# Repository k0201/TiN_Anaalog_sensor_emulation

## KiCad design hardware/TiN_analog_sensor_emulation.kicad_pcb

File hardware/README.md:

# TiN_Anaalog_sensor_emulation
Project for TiN at AGH 2019

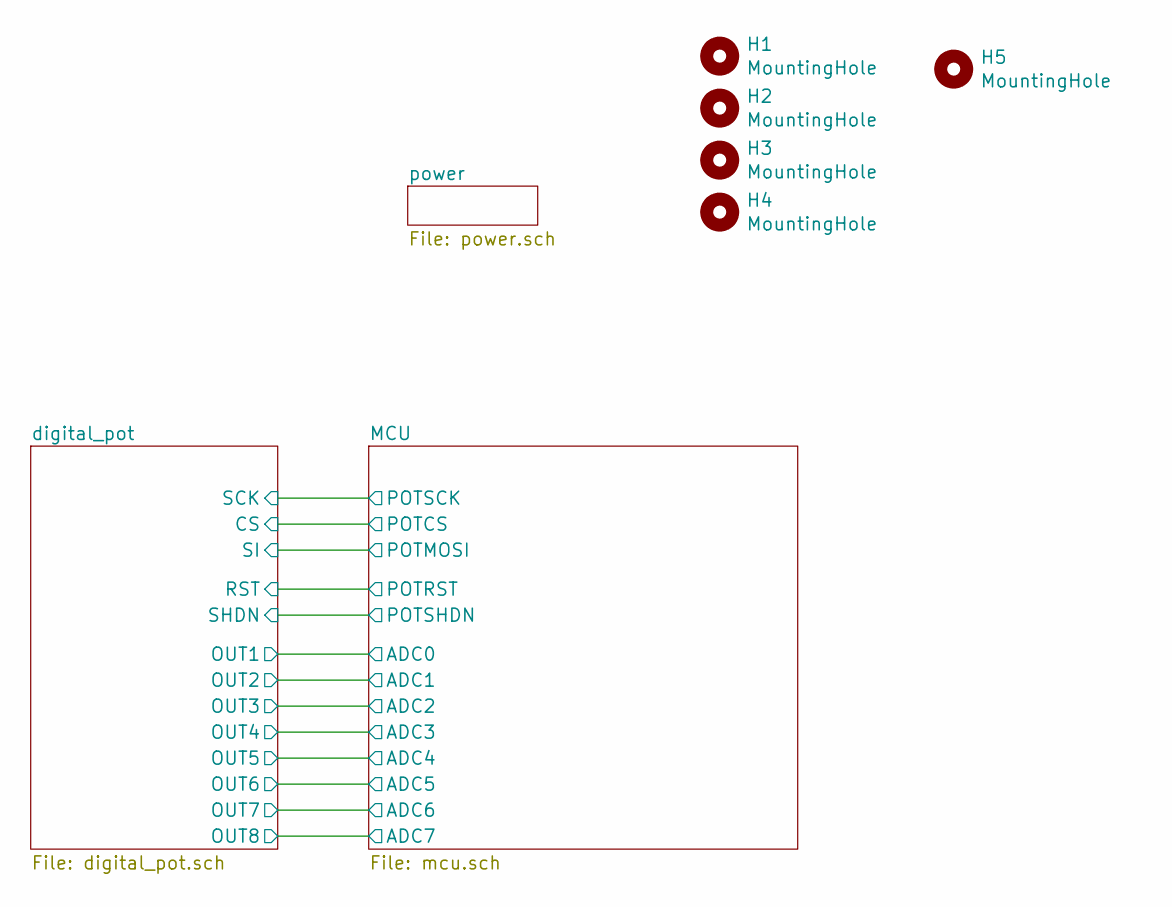
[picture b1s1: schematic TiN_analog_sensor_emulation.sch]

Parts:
H1, H2, H3, H4, H5: MountingHole; MountingHole_3.2mm_M3

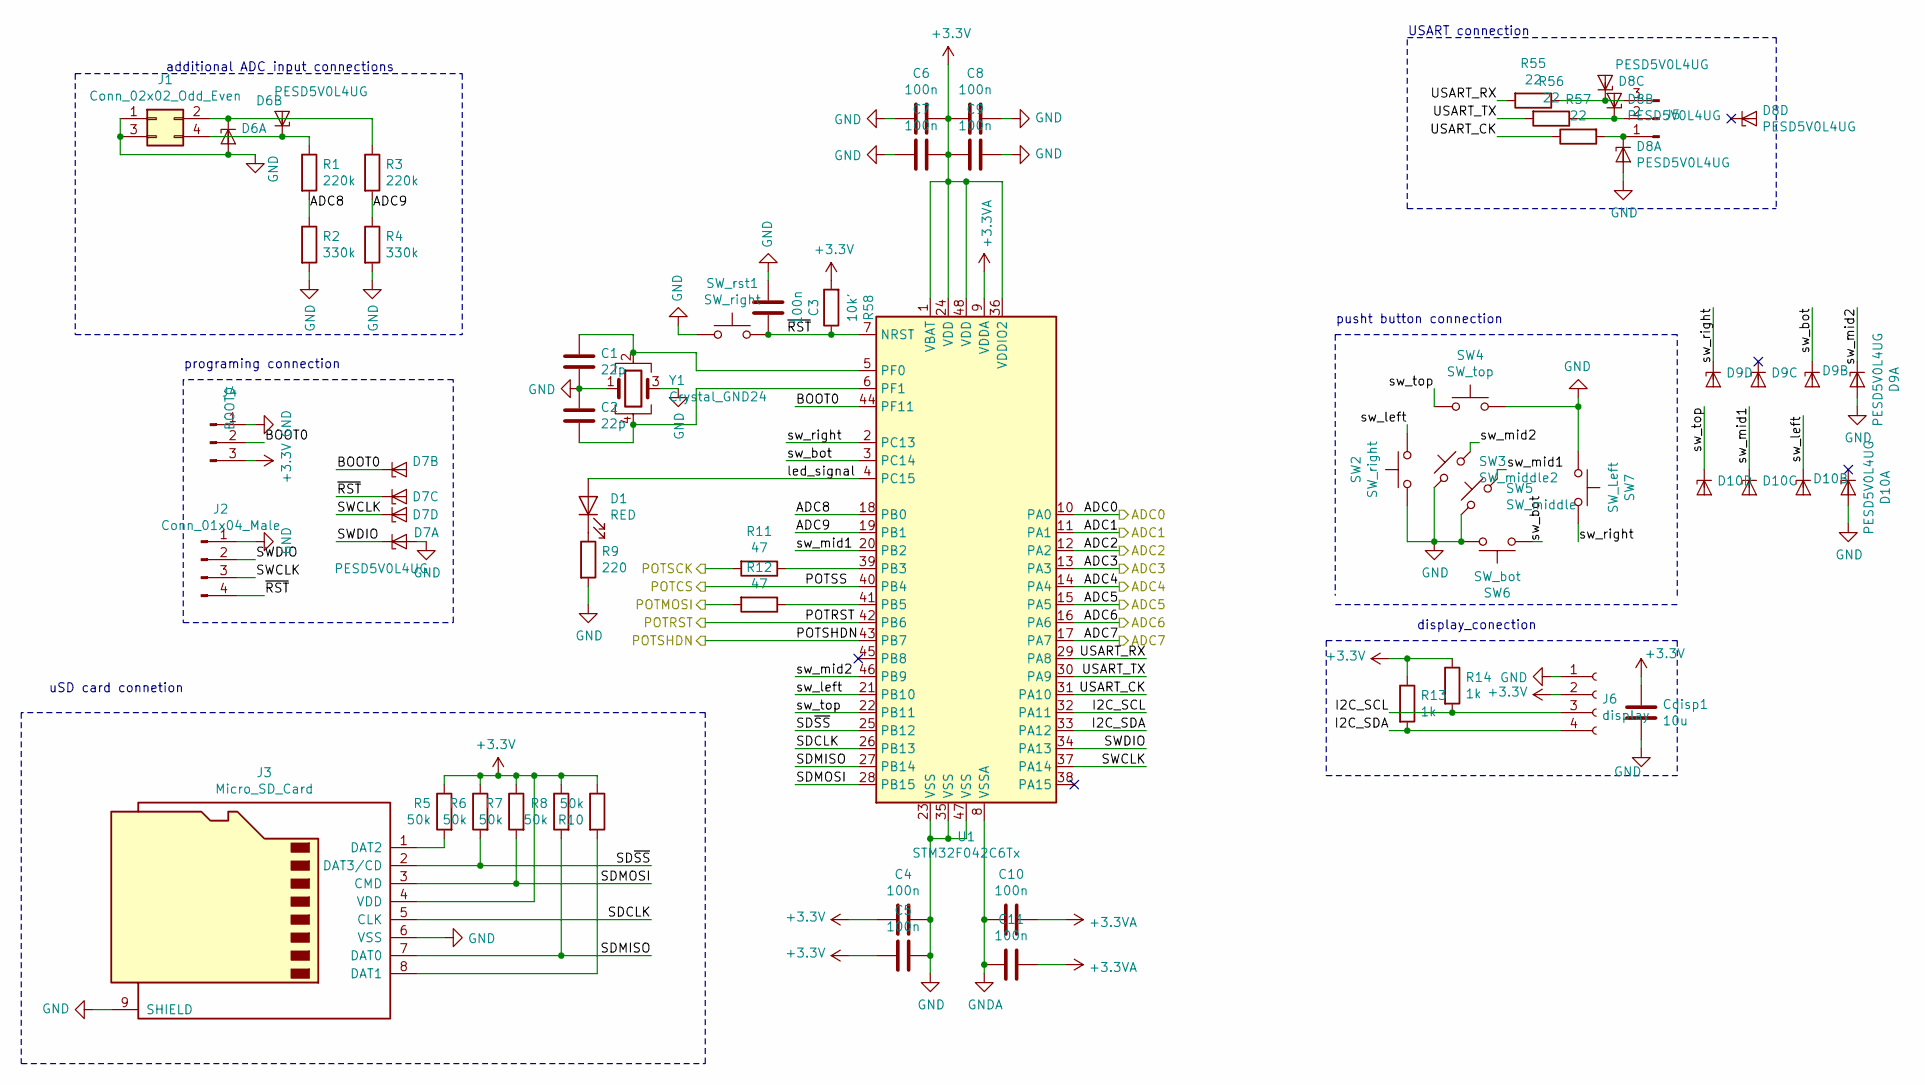
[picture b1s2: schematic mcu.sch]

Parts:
C1, C2: 22p; C_0402_1005Metric
C3, C4, C5, C6, C7, C8, C9, C10, C11: 100n; C_0603_1608Metric_Pad1.05x0.95mm_HandSolder
Cdisp1: 10u; C_0805_2012Metric
D1: RED; LED_0805_2012Metric
D6, D7, D8, D9, D10: PESD5V0L4UG; SOT-353_SC-70-5
J1: Conn_02x02_Odd_Even; PinHeader_2x02_P2.54mm_Vertical
J2: Conn_01x04_Male; PinHeader_1x04_P2.54mm_Vertical
J3: Micro_SD_Card; MOLEX_503398-1892
J4: BOOT0; PinHeader_1x03_P2.54mm_Vertical
J5: Conn_01x03_Male; PinHeader_1x03_P2.54mm_Horizontal
J6: display; PinSocket_1x04_P2.54mm_Vertical
R1, R3: 220k; R_0603_1608Metric_Pad1.05x0.95mm_HandSolder
R2, R4: 330k; R_0603_1608Metric_Pad1.05x0.95mm_HandSolder
R5, R6, R7, R8, R10: 50k; R_0603_1608Metric_Pad1.05x0.95mm_HandSolder
R9: 220; R_0603_1608Metric_Pad1.05x0.95mm_HandSolder
R11, R12: 47; R_0603_1608Metric_Pad1.05x0.95mm_HandSolder
R13, R14: 1k; R_0603_1608Metric_Pad1.05x0.95mm_HandSolder
R55, R56, R57: 22; R_0603_1608Metric_Pad1.05x0.95mm_HandSolder
R58: 10k'; R_0603_1608Metric_Pad1.05x0.95mm_HandSolder
SW2: SW_right; SW_Push_1P1T_NO_CK_KSC6xxJ
SW3: SW_middle2; SW_Push_1P1T_NO_CK_KSC6xxJ
SW4: SW_top; SW_Push_1P1T_NO_CK_KSC6xxJ
SW5: SW_middle; SW_Push_1P1T_NO_CK_KSC6xxJ
SW6: SW_bot; SW_Push_1P1T_NO_CK_KSC6xxJ
SW7: SW_Left; SW_Push_1P1T_NO_CK_KSC6xxJ
SW_rst1: SW_right; SW_Push_1P1T_NO_CK_KSC6xxJ
U1: STM32F042C6Tx; LQFP-48_7x7mm_P0.5mm
Y1: Crystal_GND24; Crystal_SMD_3225-4Pin_3.2x2.5mm

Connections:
+3.3VA: C4.2, C5.2, C6.1, C7.1, C8.2, C9.2, C10.1, C11.1, Cdisp1.1, J3.4 (VDD), J4.3, J6.2, R5.1, R6.1, R7.1, R8.1, R10.1, R13.1, R14.1, R58.2, U1.1 (VBAT), U1.9 (VDDA), U1.24 (VDD), U1.36 (VDDIO2), U1.48 (VDD); also elsewhere on the board
/MCU/ADC0: U1.10 (PA0); also elsewhere on the board
/MCU/ADC1: U1.11 (PA1); also elsewhere on the board
/MCU/ADC2: U1.12 (PA2); also elsewhere on the board
/MCU/ADC3: U1.13 (PA3); also elsewhere on the board
/MCU/ADC4: U1.14 (PA4); also elsewhere on the board
/MCU/ADC5: U1.15 (PA5); also elsewhere on the board
/MCU/ADC6: U1.16 (PA6); also elsewhere on the board
/MCU/ADC7: U1.17 (PA7); also elsewhere on the board
/MCU/ADC8: R1.2, R2.1, U1.18 (PB0)
/MCU/ADC9: R3.2, R4.1, U1.19 (PB1)
/MCU/BOOT0: D7.3 (K2), J4.2, U1.44 (PF11)
/MCU/I2C_SCL: J6.3, R14.2, U1.32 (PA11)
/MCU/I2C_SDA: J6.4, R13.2, U1.33 (PA12)
/MCU/POTMOSI: R12.2; also elsewhere on the board
/MCU/POTRST: U1.42 (PB6); also elsewhere on the board
/MCU/POTSCK: R11.2; also elsewhere on the board
/MCU/POTSHDN: U1.43 (PB7); also elsewhere on the board
/MCU/SDCLK: J3.5 (CLK), U1.26 (PB13)
/MCU/SDMISO: J3.7 (DAT0), R8.2, U1.27 (PB14)
/MCU/SDMOSI: J3.3 (CMD), R7.2, U1.28 (PB15)
/MCU/SD~SS: J3.2 (DAT3/CD), R6.2, U1.25 (PB12)
/MCU/SWCLK: D7.5 (K4), J2.3, U1.37 (PA14)
/MCU/SWDIO: D7.1 (K1), J2.2, U1.34 (PA13)
/MCU/USART_CK: R57.1, U1.31 (PA10)
/MCU/USART_RX: R55.2, U1.29 (PA8)
/MCU/USART_TX: R56.2, U1.30 (PA9)
/MCU/led_signal: D1.2 (A), U1.4 (PC15)
/MCU/sw_bot: D9.3 (K2), SW6.1, U1.3 (PC14)
/MCU/sw_left: D10.3 (K2), SW2.2, U1.21 (PB10)
/MCU/sw_mid1: D10.4 (K3), SW5.2, U1.20 (PB2)
/MCU/sw_mid2: D9.1 (K1), SW3.2, U1.46 (PB9)
/MCU/sw_right: D9.5 (K4), SW7.2, U1.2 (PC13)
/MCU/sw_top: D10.5 (K4), SW4.1, U1.22 (PB11)
/MCU/~RST: C3.1, D7.4 (K3), J2.4, R58.1, SW_rst1.2, U1.7 (NRST)
/digital_pot/CS: U1.40 (PB4); also elsewhere on the board
/digital_pot/pot7: D6.5 (K4); also elsewhere on the board
/digital_pot/pot8: D6.4 (K3); also elsewhere on the board
GND: C1.2, C2.1, C3.2, C4.1, C5.1, C6.2, C7.2, C8.1, C9.1, C10.2, C11.2, Cdisp1.2, D6.2 (A), D7.2 (A), D8.2 (A), D9.2 (A), D10.2 (A), J1.1, J1.3, J2.1, J3.6 (VSS), J3.9 (SHIELD), J4.1, J6.1, R2.2, R4.2, R9.2, SW2.1, SW3.1, SW4.2, SW5.1, SW6.2, SW7.1, SW_rst1.1, U1.8 (VSSA), U1.23 (VSS), U1.35 (VSS), U1.47 (VSS), Y1.1, Y1.3; also elsewhere on the board
unnamed: C1.1, U1.5 (PF0), Y1.2
unnamed: C2.2, U1.6 (PF1), Y1.4
unnamed: D1.1 (K), R9.1
unnamed: D6.1 (K1), J1.2, R3.1
unnamed: D6.3 (K2), J1.4, R1.1
unnamed: D8.1 (K1), J5.1, R57.2
unnamed: D8.3 (K2), J5.2, R56.1
unnamed: D8.4 (K3), J5.3, R55.1
unnamed: J3.1 (DAT2), R5.2
unnamed: J3.8 (DAT1), R10.2
unnamed: R11.1, U1.39 (PB3)
unnamed: R12.1, U1.41 (PB5)

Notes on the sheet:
display_conection
pusht button connection
uSD card connetion
programing connection
USART connection
additional ADC input connections

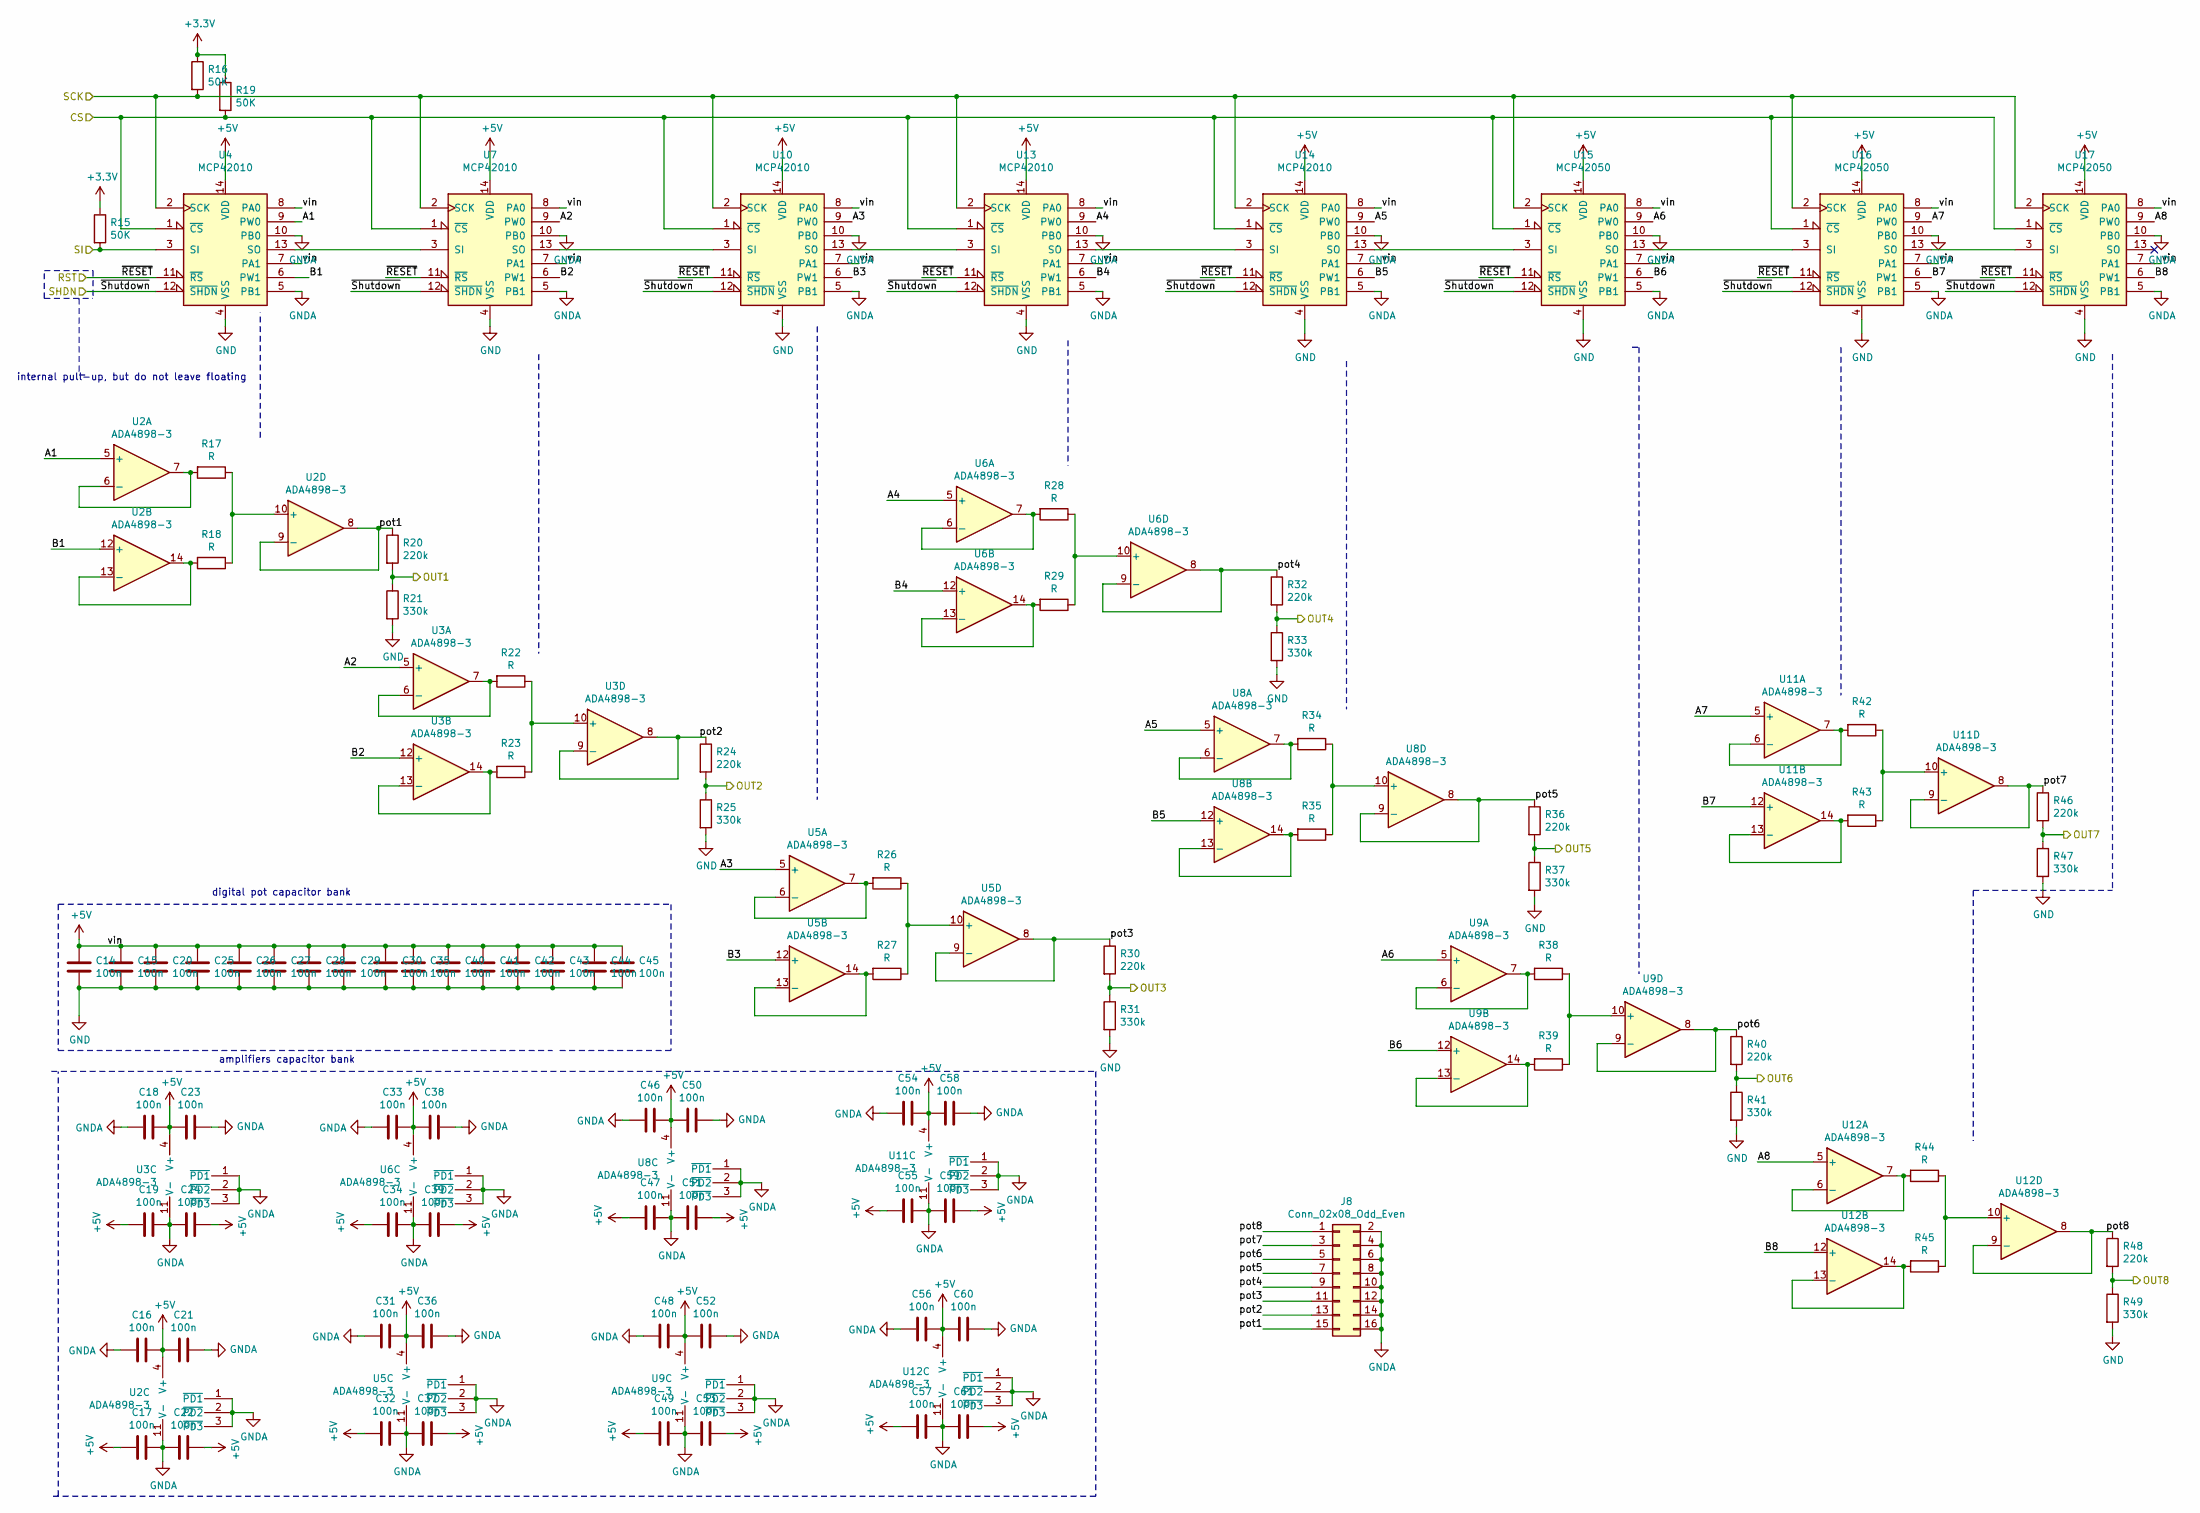
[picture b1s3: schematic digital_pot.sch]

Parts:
C14, C15, C16, C17, C18, C19, C20, C21, C22, C23, C24, C25, C26, C27, C28, C29, C30, C31, C32, C33, C34, C35, C36, C37, C38, C39, C40, C41, C42, C43, C44, C45, C46, C47, C48, C49, C50, C51, C52, C53, C54, C55, C56, C57, C58, C59, C60, C61: 100n; C_0603_1608Metric_Pad1.05x0.95mm_HandSolder
J8: Conn_02x08_Odd_Even; PinHeader_2x08_P2.54mm_Vertical
R15, R16, R19: 50K; R_0603_1608Metric_Pad1.05x0.95mm_HandSolder
R17, R18, R22, R23, R26, R27, R28, R29, R34, R35, R38, R39, R42, R43, R44, R45: R; R_0603_1608Metric_Pad1.05x0.95mm_HandSolder
R20, R24, R30, R32, R36, R40, R46, R48: 220k; R_0603_1608Metric_Pad1.05x0.95mm_HandSolder
R21, R25, R31, R33, R37, R41, R47, R49: 330k; R_0603_1608Metric_Pad1.05x0.95mm_HandSolder
U2, U3, U5, U6, U8, U9, U11, U12: ADA4898-3; SOIC-14_3.9x8.7mm_P1.27mm
U4, U7, U10, U13, U14: MCP42010; SOIC-14_3.9x8.7mm_P1.27mm
U15, U16, U17: MCP42050; SOIC-14_3.9x8.7mm_P1.27mm

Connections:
+3.3VA: R15.1, R16.1, R19.1; also elsewhere on the board
/MCU/ADC0: R20.2, R21.1; also elsewhere on the board
/MCU/ADC1: R24.2, R25.1; also elsewhere on the board
/MCU/ADC2: R30.2, R31.1; also elsewhere on the board
/MCU/ADC3: R32.2, R33.1; also elsewhere on the board
/MCU/ADC4: R36.2, R37.1; also elsewhere on the board
/MCU/ADC5: R40.2, R41.1; also elsewhere on the board
/MCU/ADC6: R46.2, R47.1; also elsewhere on the board
/MCU/ADC7: R48.2, R49.1; also elsewhere on the board
/MCU/POTMOSI: R15.2, U4.3 (SI); also elsewhere on the board
/MCU/POTRST: U4.11 (~RS), U7.11 (~RS), U10.11 (~RS), U13.11 (~RS), U14.11 (~RS), U15.11 (~RS), U16.11 (~RS), U17.11 (~RS); also elsewhere on the board
/MCU/POTSCK: R16.2, U4.2 (SCK), U7.2 (SCK), U10.2 (SCK), U13.2 (SCK), U14.2 (SCK), U15.2 (SCK), U16.2 (SCK), U17.2 (SCK); also elsewhere on the board
/MCU/POTSHDN: U4.12 (~SHDN), U7.12 (~SHDN), U10.12 (~SHDN), U13.12 (~SHDN), U14.12 (~SHDN), U15.12 (~SHDN), U16.12 (~SHDN), U17.12 (~SHDN); also elsewhere on the board
/digital_pot/A1: U2.5 (+), U4.9 (PW0)
/digital_pot/A2: U3.5 (+), U7.9 (PW0)
/digital_pot/A3: U5.5 (+), U10.9 (PW0)
/digital_pot/A4: U6.5 (+), U13.9 (PW0)
/digital_pot/A5: U8.5 (+), U14.9 (PW0)
/digital_pot/A6: U9.5 (+), U15.9 (PW0)
/digital_pot/A7: U11.5 (+), U16.9 (PW0)
/digital_pot/A8: U12.5 (+), U17.9 (PW0)
/digital_pot/B1: U2.12 (+), U4.6 (PW1)
/digital_pot/B2: U3.12 (+), U7.6 (PW1)
/digital_pot/B3: U5.12 (+), U10.6 (PW1)
/digital_pot/B4: U6.12 (+), U13.6 (PW1)
/digital_pot/B5: U8.12 (+), U14.6 (PW1)
/digital_pot/B6: U9.12 (+), U15.6 (PW1)
/digital_pot/B7: U11.12 (+), U16.6 (PW1)
/digital_pot/B8: U12.12 (+), U17.6 (PW1)
/digital_pot/CS: R19.2, U4.1 (~CS), U7.1 (~CS), U10.1 (~CS), U13.1 (~CS), U14.1 (~CS), U15.1 (~CS), U16.1 (~CS), U17.1 (~CS); also elsewhere on the board
/digital_pot/pot1: J8.15, R20.1, U2.8, U2.9 (-); also elsewhere on the board
/digital_pot/pot2: J8.13, R24.1, U3.8, U3.9 (-); also elsewhere on the board
/digital_pot/pot3: J8.11, R30.1, U5.8, U5.9 (-); also elsewhere on the board
/digital_pot/pot4: J8.9, R32.1, U6.8, U6.9 (-); also elsewhere on the board
/digital_pot/pot5: J8.7, R36.1, U8.8, U8.9 (-); also elsewhere on the board
/digital_pot/pot6: J8.5, R40.1, U9.8, U9.9 (-); also elsewhere on the board
/digital_pot/pot7: J8.3, R46.1, U11.8, U11.9 (-); also elsewhere on the board
/digital_pot/pot8: J8.1, R48.1, U12.8, U12.9 (-); also elsewhere on the board
GND: C14.1, C15.1, C16.2, C17.1, C18.2, C19.1, C20.1, C21.1, C22.2, C23.1, C24.2, C25.1, C26.1, C27.1, C28.1, C29.1, C30.1, C31.2, C32.1, C33.2, C34.1, C35.1, C36.1, C37.2, C38.1, C39.2, C40.1, C41.1, C42.1, C43.1, C44.1, C45.1, C46.2, C47.1, C48.2, C49.1, C50.1, C51.2, C52.1, C53.2, C54.2, C55.1, C56.2, C57.1, C58.1, C59.2, C60.1, C61.2, J8.2, J8.4, J8.6, J8.8, J8.10, J8.12, J8.14, J8.16, R21.2, R25.2, R31.2, R33.2, R37.2, R41.2, R47.2, R49.2, U2.1 (~PD1), U2.2 (~PD2), U2.3 (~PD3), U2.11 (V-), U3.1 (~PD1), U3.2 (~PD2), U3.3 (~PD3), U3.11 (V-), U4.4 (VSS), U4.5 (PB1), U4.10 (PB0), U5.1 (~PD1), U5.2 (~PD2), U5.3 (~PD3), U5.11 (V-), U6.1 (~PD1), U6.2 (~PD2), U6.3 (~PD3), U6.11 (V-), U7.4 (VSS), U7.5 (PB1), U7.10 (PB0), U8.1 (~PD1), U8.2 (~PD2), U8.3 (~PD3), U8.11 (V-), U9.1 (~PD1), U9.2 (~PD2), U9.3 (~PD3), U9.11 (V-), U10.4 (VSS), U10.5 (PB1), U10.10 (PB0), U11.1 (~PD1), U11.2 (~PD2), U11.3 (~PD3), U11.11 (V-), U12.1 (~PD1), U12.2 (~PD2), U12.3 (~PD3), U12.11 (V-), U13.4 (VSS), U13.5 (PB1), U13.10 (PB0), U14.4 (VSS), U14.5 (PB1), U14.10 (PB0), U15.4 (VSS), U15.5 (PB1), U15.10 (PB0), U16.4 (VSS), U16.5 (PB1), U16.10 (PB0), U17.4 (VSS), U17.5 (PB1), U17.10 (PB0); also elsewhere on the board
unnamed: R17.1, R18.1, U2.10 (+)
unnamed: R17.2, U2.6 (-), U2.7
unnamed: R18.2, U2.13 (-), U2.14
unnamed: R22.1, R23.1, U3.10 (+)
unnamed: R22.2, U3.6 (-), U3.7
unnamed: R23.2, U3.13 (-), U3.14
unnamed: R26.1, R27.1, U5.10 (+)
unnamed: R26.2, U5.6 (-), U5.7
unnamed: R27.2, U5.13 (-), U5.14
unnamed: R28.1, R29.1, U6.10 (+)
unnamed: R28.2, U6.6 (-), U6.7
unnamed: R29.2, U6.13 (-), U6.14
unnamed: R34.1, R35.1, U8.10 (+)
unnamed: R34.2, U8.6 (-), U8.7
unnamed: R35.2, U8.13 (-), U8.14
unnamed: R38.1, R39.1, U9.10 (+)
unnamed: R38.2, U9.6 (-), U9.7
unnamed: R39.2, U9.13 (-), U9.14
unnamed: R42.1, R43.1, U11.10 (+)
unnamed: R42.2, U11.6 (-), U11.7
unnamed: R43.2, U11.13 (-), U11.14
unnamed: R44.1, R45.1, U12.10 (+)
unnamed: R44.2, U12.6 (-), U12.7
unnamed: R45.2, U12.13 (-), U12.14
unnamed: U4.13 (SO), U7.3 (SI)
unnamed: U7.13 (SO), U10.3 (SI)
unnamed: U10.13 (SO), U13.3 (SI)
unnamed: U13.13 (SO), U14.3 (SI)
unnamed: U14.13 (SO), U15.3 (SI)
unnamed: U15.13 (SO), U16.3 (SI)
unnamed: U16.13 (SO), U17.3 (SI)

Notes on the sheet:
internal pull-up, but do not leave floating
digital pot capacitor bank
amplifiers capacitor bank

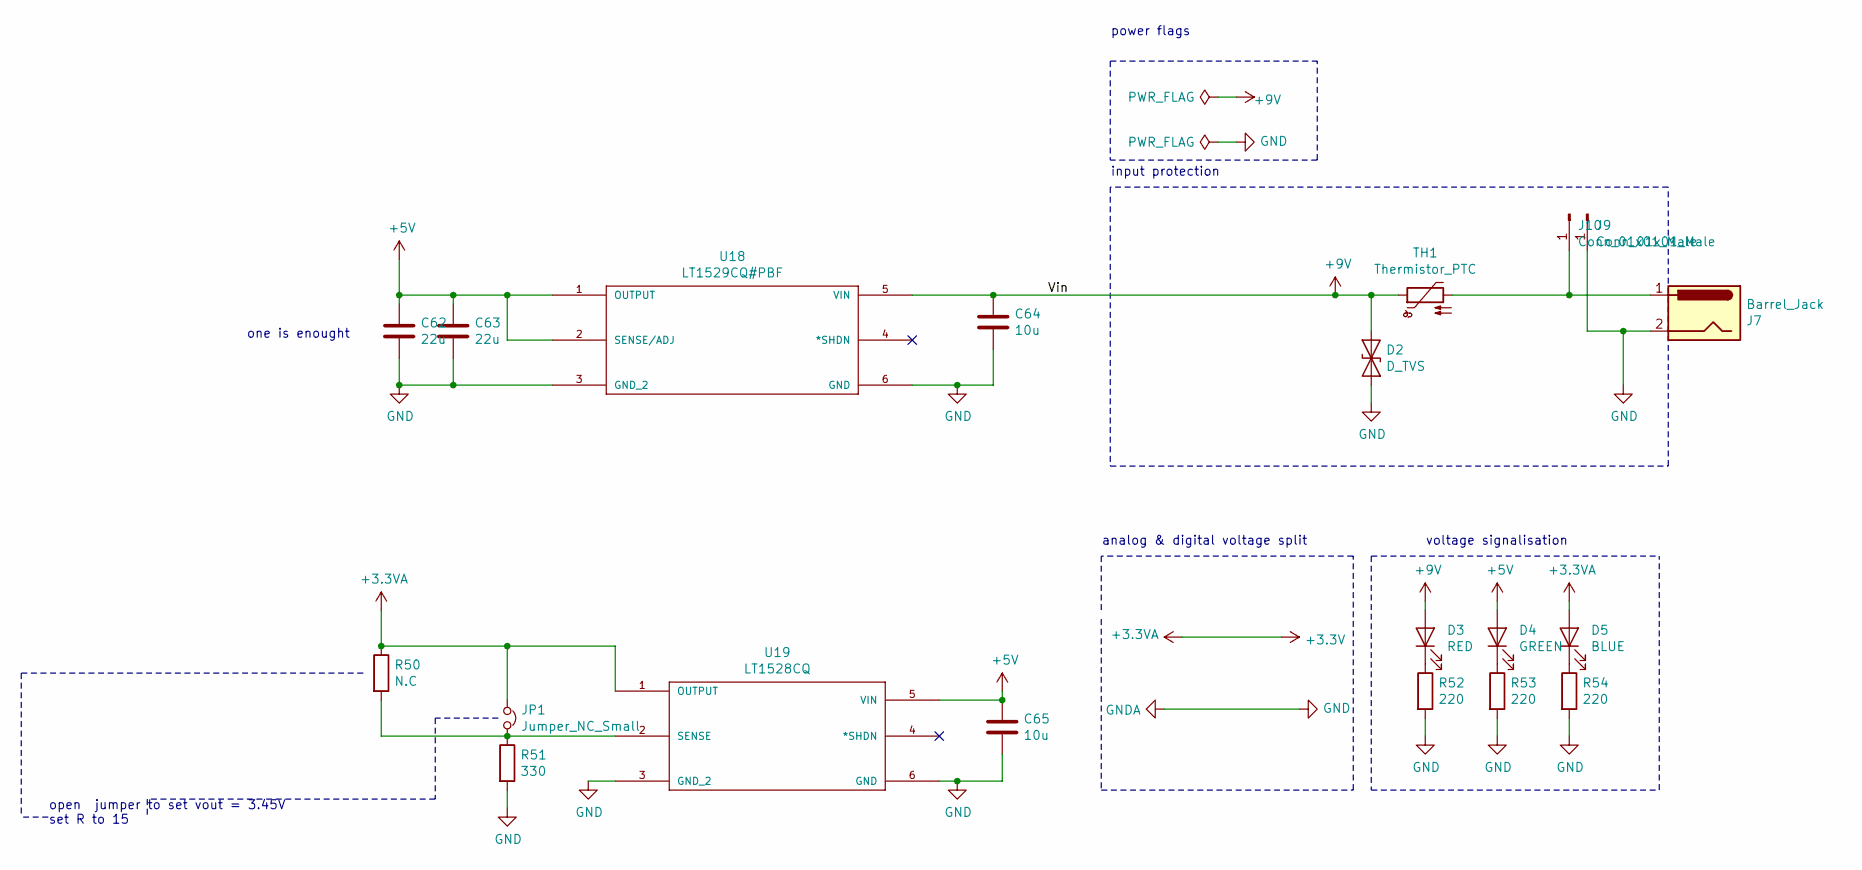
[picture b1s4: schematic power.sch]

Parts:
C62, C63: 22u; C_0805_2012Metric_Pad1.15x1.40mm_HandSolder
C64, C65: 10u; C_0805_2012Metric_Pad1.15x1.40mm_HandSolder
D2: D_TVS; D_SMB
D3: RED; LED_0805_2012Metric
D4: GREEN; LED_0805_2012Metric
D5: BLUE; LED_0805_2012Metric
J7: Barrel_Jack; BarrelJack_Horizontal
J9, J10: Conn_01x01_Male; SolderWirePad_1x01_Drill2.5mm
JP1: Jumper_NC_Small; SolderJumper-2_P1.3mm_Bridged_Pad1.0x1.5mm
R50: N.C; R_0603_1608Metric_Pad1.05x0.95mm_HandSolder
R51: 330; R_0603_1608Metric_Pad1.05x0.95mm_HandSolder
R52, R53, R54: 220; R_0603_1608Metric_Pad1.05x0.95mm_HandSolder
TH1: Thermistor_PTC; Fuse_1812_4532Metric
U18: LT1529CQ#PBF; DDPAK-5_Q
U19: LT1528CQ; DDPAK-5_Q

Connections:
+3.3VA: D5.2 (A), JP1.1, R50.1, U19.1 (OUTPUT); also elsewhere on the board
+9V: C64.1, D2.1 (A1), D3.2 (A), TH1.1, U18.5 (VIN)
GND: C62.2, C63.2, C64.2, C65.2, D2.2 (A2), J7.2, J9.1, R51.2, R52.2, R53.2, R54.2, U18.3 (GND_2), U18.6 (GND), U19.3 (GND_2), U19.6 (GND); also elsewhere on the board
unnamed: D3.1 (K), R52.1
unnamed: D4.1 (K), R53.1
unnamed: D5.1 (K), R54.1
unnamed: J7.1, J10.1, TH1.2
unnamed: JP1.2, R50.2, R51.1, U19.2 (SENSE)

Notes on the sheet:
open jumper to set vout = 3.45V set R to 15
one is enought
input protection
voltage signalisation
analog & digital voltage split
power flags

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
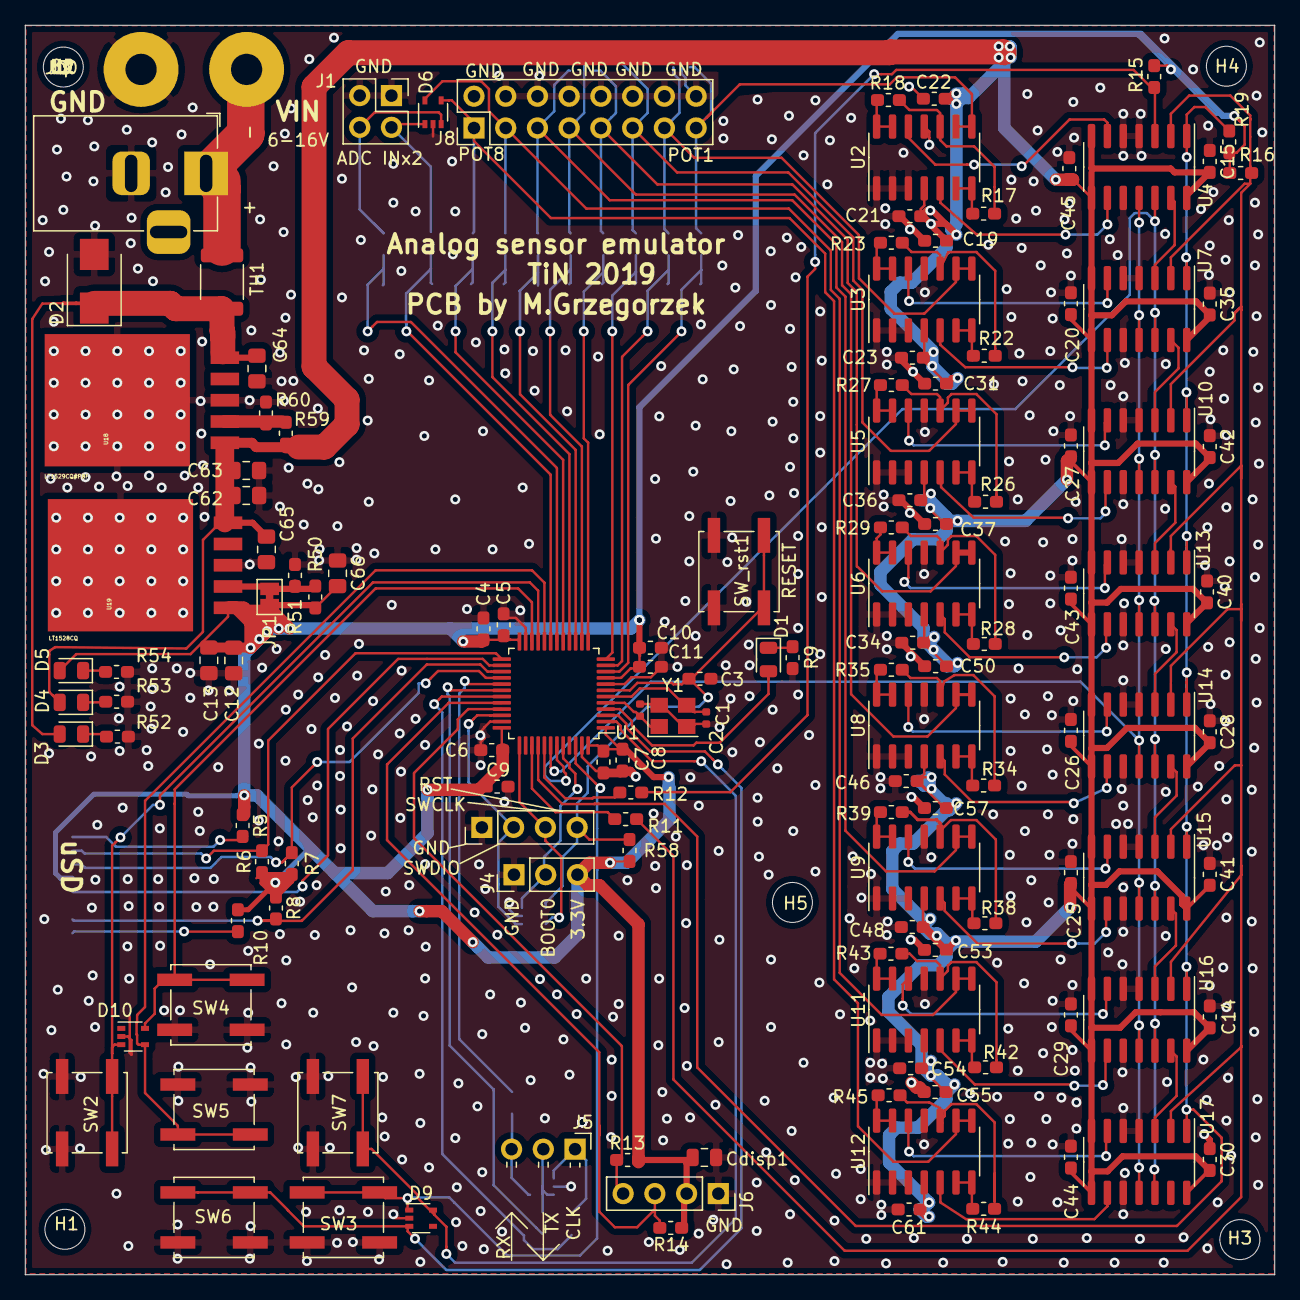
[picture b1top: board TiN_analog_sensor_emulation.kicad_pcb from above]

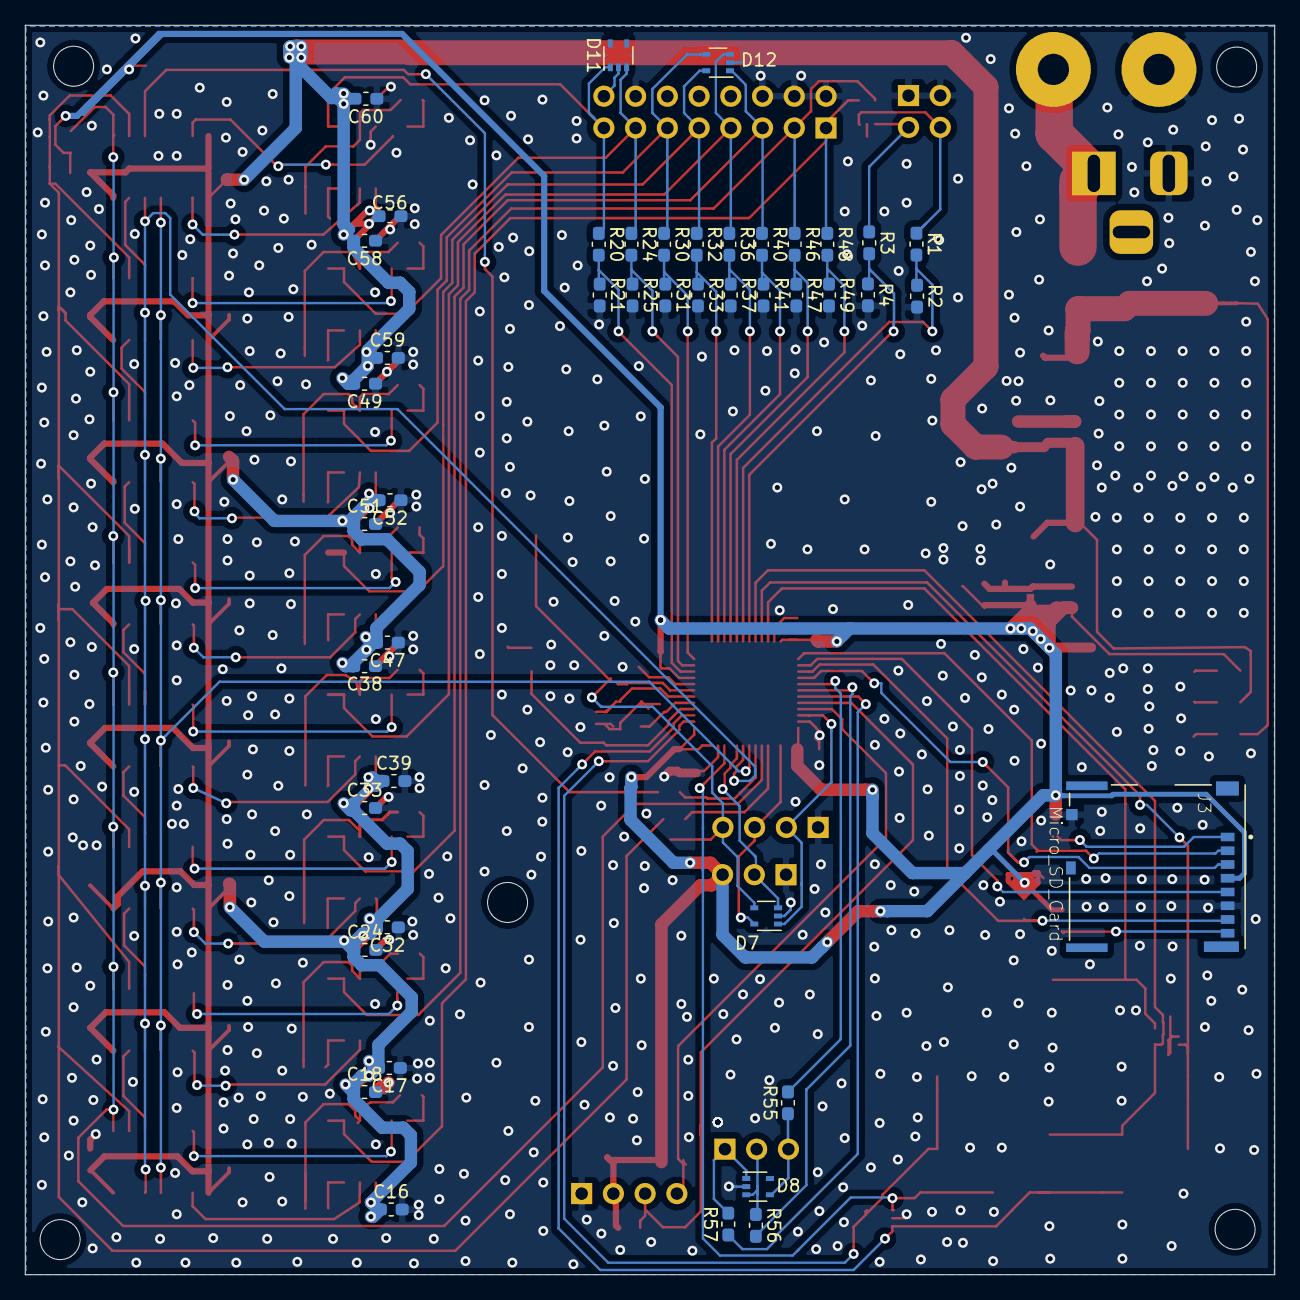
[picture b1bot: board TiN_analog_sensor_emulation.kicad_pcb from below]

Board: 2 copper layers, 100.0 x 100.0 mm, 183 parts (44 on the bottom side), 112 nets.

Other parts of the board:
C12, C13, C66: 22u; C_0805_2012Metric_Pad1.15x1.40mm_HandSolder
D11, D12: PESD5V0L4UG; SOT-353_SC-70-5
R59: 110k; R_0603_1608Metric_Pad1.05x0.95mm_HandSolder
R60: 330k; R_0603_1608Metric_Pad1.05x0.95mm_HandSolder

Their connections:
+3.3VA: C12.2, C13.2, C66.2; also elsewhere on the board
/digital_pot/pot1: D11.1; also elsewhere on the board
/digital_pot/pot2: D11.3; also elsewhere on the board
/digital_pot/pot3: D12.4; also elsewhere on the board
/digital_pot/pot4: D12.5; also elsewhere on the board
/digital_pot/pot5: D12.3; also elsewhere on the board
/digital_pot/pot6: D12.1; also elsewhere on the board
GND: C12.1, C13.1, C66.1, D11.2, D12.2, R60.2; also elsewhere on the board

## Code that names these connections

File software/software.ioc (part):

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Mcu.Name=STM32F042C(4-6)Tx
Mcu.Package=LQFP48
Mcu.UserName=STM32F042C6Tx
PA0.Mode=IN0
PA0.Signal=ADC_IN0
PA1.Mode=IN1
PA1.Signal=ADC_IN1
PA10.Mode=Synchronous
PA10.Signal=USART1_RX
PA11.Mode=I2C
PA11.Signal=I2C1_SCL
PA12.Mode=I2C
PA12.Signal=I2C1_SDA
PA13.Mode=Serial_Wire
PA13.Signal=SYS_SWDIO
PA14.Mode=Serial_Wire
PA14.Signal=SYS_SWCLK
PA2.Mode=IN2
PA2.Signal=ADC_IN2
PA3.Mode=IN3
PA3.Signal=ADC_IN3
PA4.Mode=IN4
PA4.Signal=ADC_IN4
PA5.Mode=IN5
PA5.Signal=ADC_IN5
PA6.Mode=IN6
PA6.Signal=ADC_IN6
PA7.Mode=IN7
PA7.Signal=ADC_IN7
PA8.Mode=Synchronous
PA8.Signal=USART1_CK
PA9.Mode=Synchronous
PA9.Signal=USART1_TX
PB0.Mode=IN8
PB0.Signal=ADC_IN8
PB1.Mode=IN9
PB1.Signal=ADC_IN9
PB10.GPIOParameters=GPIO_Label
PB10.GPIO_Label=SW4
PB10.Signal=GPIO_Input
PB11.GPIOParameters=GPIO_Label
PB11.GPIO_Label=SW5
PB11.Signal=GPIO_Input
PB12.GPIOParameters=GPIO_Label
PB12.GPIO_Label=SS2
PB12.Signal=GPIO_Output
PB13.Mode=Full_Duplex_Master
PB13.Signal=SPI2_SCK
PB14.Mode=Full_Duplex_Master
PB14.Signal=SPI2_MISO
PB15.Mode=Full_Duplex_Master
PB15.Signal=SPI2_MOSI
PB2.GPIOParameters=GPIO_Label
PB2.GPIO_Label=SW2
PB2.Signal=GPIO_Input
PB3.Mode=TX_Only_Simplex_Unidirect_Master
PB3.Signal=SPI1_SCK
PB4.GPIOParameters=GPIO_Label
PB4.GPIO_Label=SS1
PB4.Signal=GPIO_Output
PB5.Mode=TX_Only_Simplex_Unidirect_Master
PB5.Signal=SPI1_MOSI
PB6.GPIOParameters=GPIO_Label
PB6.GPIO_Label=POT RST
PB6.Signal=GPIO_Input
PB7.GPIOParameters=GPIO_Label
PB7.GPIO_Label=POT SHDN
PB7.Signal=GPIO_Input
PB8.GPIOParameters=GPIO_Label
PB8.GPIO_Label=BOOT0
PB8.Signal=GPIO_Input
PB9.GPIOParameters=GPIO_Label
PB9.GPIO_Label=SW0
PB9.Signal=GPIO_Input
PC13.GPIOParameters=GPIO_Label
PC13.GPIO_Label=SW1
PC13.Signal=GPIO_Input
PC14OSC32_IN.GPIOParameters=GPIO_Label
PC14OSC32_IN.GPIO_Label=SW2
PC14OSC32_IN.Signal=GPIO_Input
PC15OSC32_OUT.GPIOParameters=GPIO_Label
PC15OSC32_OUT.GPIO_Label=LED
PC15OSC32_OUT.Signal=GPIO_Output
PF0-OSC_IN.Mode=HSE-External-Oscillator
PF0-OSC_IN.Signal=RCC_OSC_IN
PF1-OSC_OUT.Mode=HSE-External-Oscillator
PF1-OSC_OUT.Signal=RCC_OSC_OUT
board=custom

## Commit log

2019-05-17 stworzenie projektu, dodanie potencjometrów cyfrowych
2019-05-17 Praca nad sch, dodana sekcja zasilania i karta sd
2019-05-17 dalsza praca nad sch, przypisanie pinów
2019-05-17 przeniosiono do folderu hardware
2019-05-18 dodano wyjscie programatora, przyciski ustalono wysjcie i2c, dodany plik CubeMX z pinouterm
2019-05-18 DRC przechodzi dorzucone złącze do wyświetlacza na i2c oraz jeden push button
2019-05-18 przypisano footprinty
2019-05-18 Dodenie pullup do spi i i2c
2019-05-18 pierwszy układ PCB
2019-05-19 update pinoutu, zmiany footprintów
2019-05-19 dodanie zabezpieczen portów i dzialniki napiec na wejsciach adc
2019-05-19 mała poprawka przy kondensatorach od opampow
2019-05-19 trwa układanie, dodane złacze golpin
2019-05-19 layout gotów, do wyeliminowania błedy DRC
2019-05-19 dodany otwór do montażu wyświetlacza
2019-05-20 update top overlay, drc przechodzi, dodny shielding wokół ścieżek zegarowych, dodane zdjęcia płytki
2019-05-20 drobne poprawki w przelotkach
2019-05-24 dodano gerbery i obrócono kartę uSD (teraz na bottom)
2019-06-15 dodano poprawki błędów znalezionych podczas montażu
2019-06-26 dodanie PDF schematu
